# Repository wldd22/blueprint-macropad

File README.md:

# Custom Macropad
A custom macropad with remappable numpad keys. Has 0-9 plus modifiers. Made for [Hackclub's Blueprint](https://blueprint.hackclub.com/)

## Details
PCB made using KiCAD \
Case made using Fusion360 \
Firmware made using KMK

## About
This was my first hardware project involving CAD. I've only ever worked on breadboards with an Arduino before. So, I had to learn KiCAD and Fusion from scratch to design the board and case.

## Images

### CAD

### Schematic

### PCB

### Case

## BOM

- 1x Seeed XIAO RP2040 (Microcontroller)
- 16x Cherry MX Switches
- 16x Blank White DSA Keycaps
- 3x SK6812 MINI-E LEDs
- 4x M3x16 Bolt
- 4x M3 Heatset

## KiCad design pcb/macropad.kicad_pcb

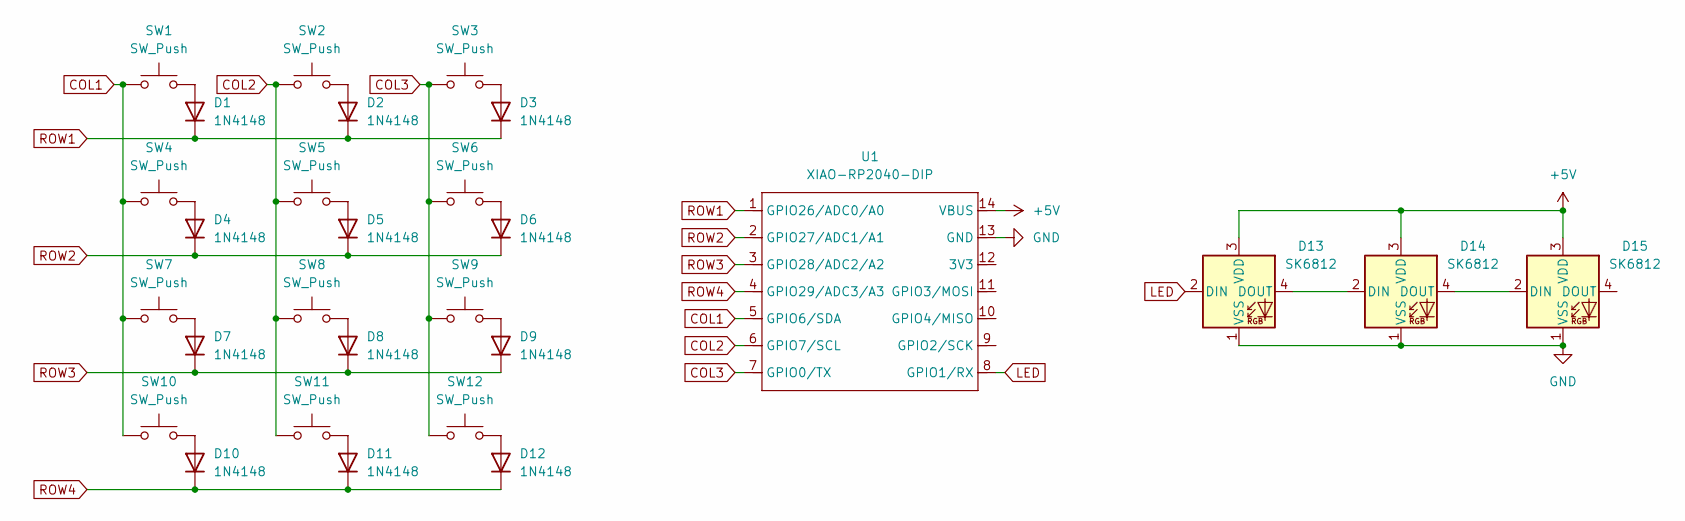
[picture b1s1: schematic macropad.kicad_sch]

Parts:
D1, D2, D3, D4, D5, D6, D7, D8, D9, D10, D11, D12: 1N4148; D_DO-35_SOD27_P7.62mm_Horizontal
D13, D14, D15: SK6812; LED_SK6812MINI_PLCC4_3.5x3.5mm_P1.75mm
SW1, SW2, SW3, SW4, SW5, SW6, SW7, SW8, SW9, SW10, SW11, SW12: SW_Push; SW_Cherry_MX_1.00u_PCB
U1: XIAO-RP2040-DIP

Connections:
+5V: D13.3 (VDD), D14.3 (VDD), D15.3 (VDD), U1.14 (VBUS)
COL1: SW1.1, SW4.1, SW7.1, SW10.1, U1.5 (GPIO6/SDA)
COL2: SW2.1, SW5.1, SW8.1, SW11.1, U1.6 (GPIO7/SCL)
COL3: SW3.1, SW6.1, SW9.1, SW12.1, U1.7 (GPIO0/TX)
GND: D13.1 (VSS), D14.1 (VSS), D15.1 (VSS), U1.13 (GND)
LED: D13.2 (DIN), U1.8 (GPIO1/RX)
unnamed: D1.2 (A), SW1.2
unnamed: D2.2 (A), SW2.2
unnamed: D3.2 (A), SW3.2
unnamed: D4.2 (A), SW4.2
unnamed: D5.2 (A), SW5.2
unnamed: D6.2 (A), SW6.2
unnamed: D7.2 (A), SW7.2
unnamed: D8.2 (A), SW8.2
unnamed: D9.2 (A), SW9.2
unnamed: D10.2 (A), SW10.2
unnamed: D11.2 (A), SW11.2
unnamed: D12.2 (A), SW12.2
unnamed: D13.4 (DOUT), D14.2 (DIN)
unnamed: D14.4 (DOUT), D15.2 (DIN)
ROW1: D1.1 (K), D2.1 (K), D3.1 (K), U1.1 (GPIO26/ADC0/A0)
ROW2: D4.1 (K), D5.1 (K), D6.1 (K), U1.2 (GPIO27/ADC1/A1)
ROW3: D7.1 (K), D8.1 (K), D9.1 (K), U1.3 (GPIO28/ADC2/A2)
ROW4: D10.1 (K), D11.1 (K), D12.1 (K), U1.4 (GPIO29/ADC3/A3)

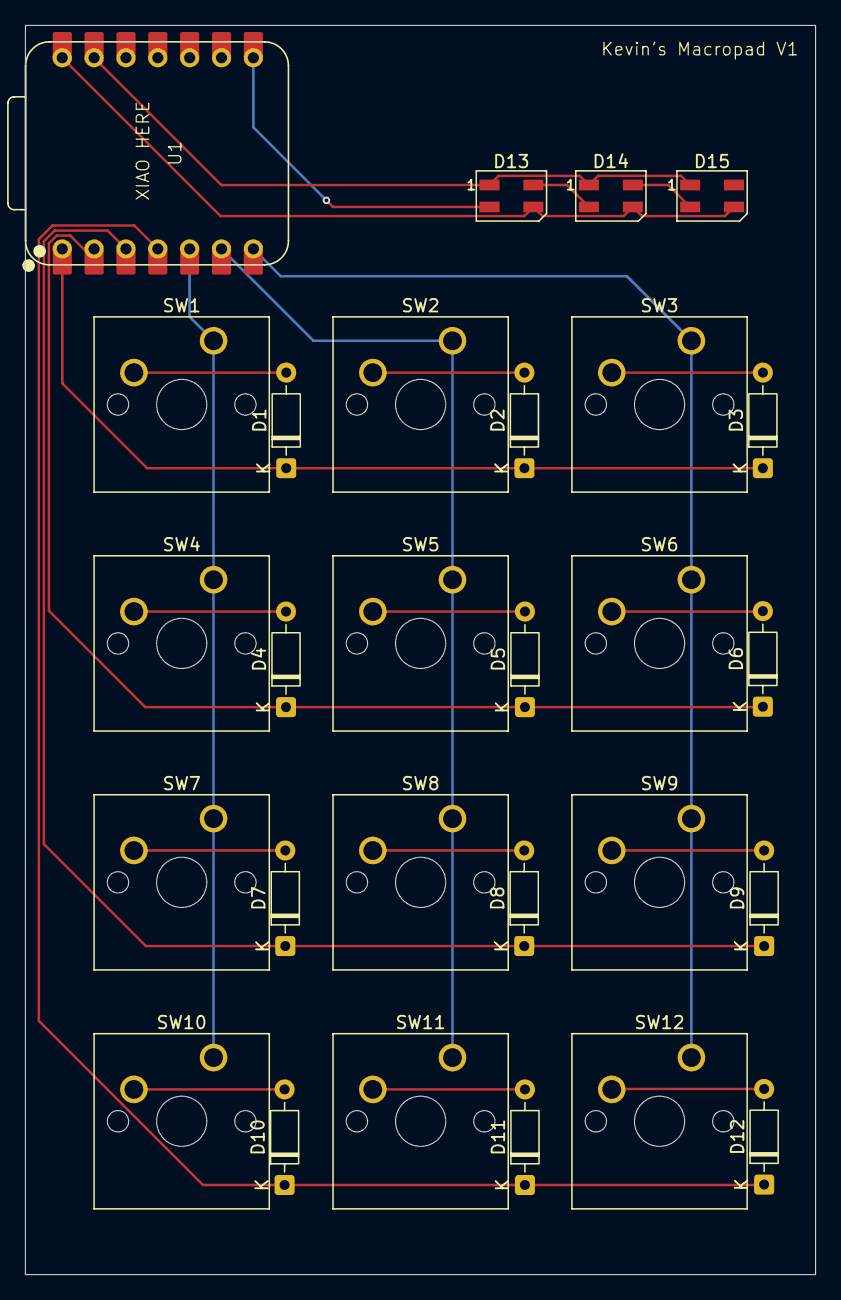
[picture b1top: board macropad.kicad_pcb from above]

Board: 2 copper layers, 63.0 x 99.6 mm, 28 parts (0 on the bottom side), 24 nets.

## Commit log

2026-01-11 Upload files
2026-01-12 Add CAD files
2026-01-12 Finalise CAD files
2026-01-12 Rename
2026-01-12 Modify README
2026-01-12 Rename files
2026-01-14 Add image
2026-01-14 Change images
2026-01-14 Add COL2ROW diodes per-key
2026-01-14 Update CAD files and screenshots
2026-01-16 Rearrange schematic and reroute PCB
2026-01-16 Update screenshots
2026-01-16 Add backups to gitignore
2026-02-08 Rearrange schematic
2026-02-08 Move OPL library
2026-02-08 Rename OPL Library
2026-02-10 Update routing image and change PCB title
2026-02-24 Update firmware
2026-02-24 Add build image
2026-02-24 Add modifier layer to firmware
2026-04-06 Remove wordmark and increase case bottom height
